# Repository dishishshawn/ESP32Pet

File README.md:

# ESP32PET

An open-source Tamagotchi, built on an ESP32 with an ST7735 LCD and physical buttons. 
A digital pet resembling me responds to feeding, playing, and dressing up. 
Stats are persistent (saved to EEPROM)

## Features
- Deep sleep (Battery powered use)
- Three-button UI (+ 1 for on and off)
- Designed for portable use

## Hardware Requirements
- ESP32 w/ EEPROM storage (ESP32 DevKit V1)
- Arduino framework (Platform IO)
- TFT LCD (ST7735)
- 3.7V LiPo battery + MCP1700 (3.3V LDO)
- 4x momentary push buttons

## Applications
- KiCAD
- Arduino IDE or PlatformIO

## Additional Notes
Decided to use the full esp32 dev kit for easy testing of new firmware/features.

## Images

## Schematic

**Top level**

**ESP32**

**Power**

**TFT LCD**

## Tamagotchi Case
[OnShape](https://cad.onshape.com/documents/7b0af2517bc8518bf7fb4dfa/w/fc1d8dcb5d67add2eca69795/e/ab74bcbcb7495b5b308ae66d)

## Demo

No demo currently

## Sponsorship

PCBWay sponsors 3D Printing and PCB assembly costs on this project during the prototyping phase!
If you are interested in their awesome fabrication services please check them out.  They offer
3D prototyping, PCB design, and assembly, as well as CNC metal fabrication.  Costs are reasonable and the quality is as good as it gets.  Thank you, PCBWay, for sponsoring me!

## License

MIT

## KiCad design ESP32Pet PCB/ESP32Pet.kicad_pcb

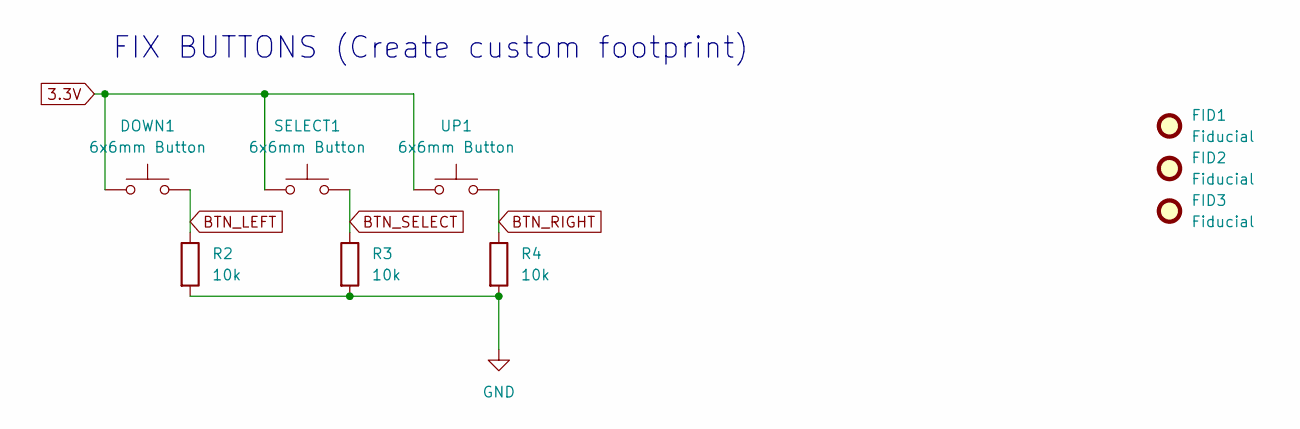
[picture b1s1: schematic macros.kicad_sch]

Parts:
DOWN1: 6x6mm Button; SW_PUSH_6mm_H5mm
FID1, FID2, FID3: Fiducial; Fiducial_0.5mm_Mask1mm
R2, R3, R4: 10k; R_Axial_DIN0204_L3.6mm_D1.6mm_P7.62mm_Horizontal
SELECT1: 6x6mm Button; SW_PUSH_6mm_H5mm
UP1: 6x6mm Button; SW_PUSH_6mm_H5mm

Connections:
3.3V: DOWN1.1, SELECT1.1, UP1.1; also elsewhere on the board
BTN_LEFT: DOWN1.2, R2.1; also elsewhere on the board
BTN_RIGHT: R4.1, UP1.2; also elsewhere on the board
BTN_SELECT: R3.1, SELECT1.2; also elsewhere on the board
GND: R2.2, R3.2, R4.2; also elsewhere on the board

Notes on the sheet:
FIX BUTTONS (Create custom footprint)

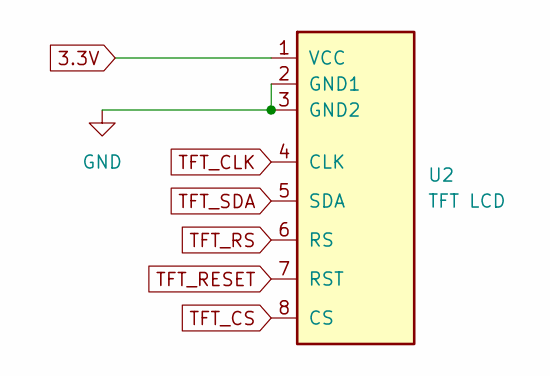
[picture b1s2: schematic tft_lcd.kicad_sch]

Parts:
U2: TFT LCD; TFT LCD 1.8inch 128x160 w_ SD Card Slot

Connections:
3.3V: U2.1 (VCC); also elsewhere on the board
GND: U2.2 (GND1), U2.3 (GND2); also elsewhere on the board
TFT_CLK: U2.4 (CLK); also elsewhere on the board
TFT_CS: U2.8 (CS); also elsewhere on the board
TFT_RESET: U2.7 (RST); also elsewhere on the board
TFT_RS: U2.6 (RS); also elsewhere on the board
TFT_SDA: U2.5 (SDA); also elsewhere on the board

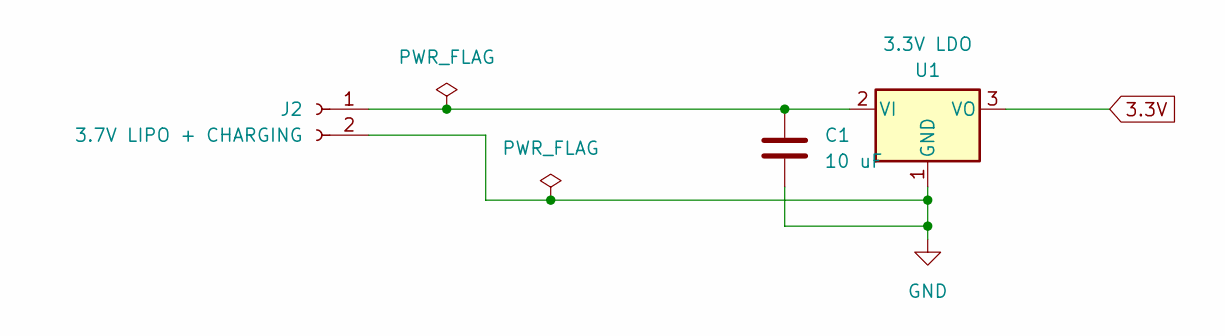
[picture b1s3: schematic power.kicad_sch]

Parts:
C1: 10 uF; CP_Radial_D4.0mm_P1.50mm
J2: 3.7V LIPO + CHARGING; PinHeader_1x02_P2.54mm_Vertical
U1: 3.3V LDO; TO-92_Inline

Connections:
3.3V: U1.3 (VO); also elsewhere on the board
GND: C1.1, J2.2, U1.1 (GND); also elsewhere on the board
unnamed: C1.2, J2.1, U1.2 (VI)

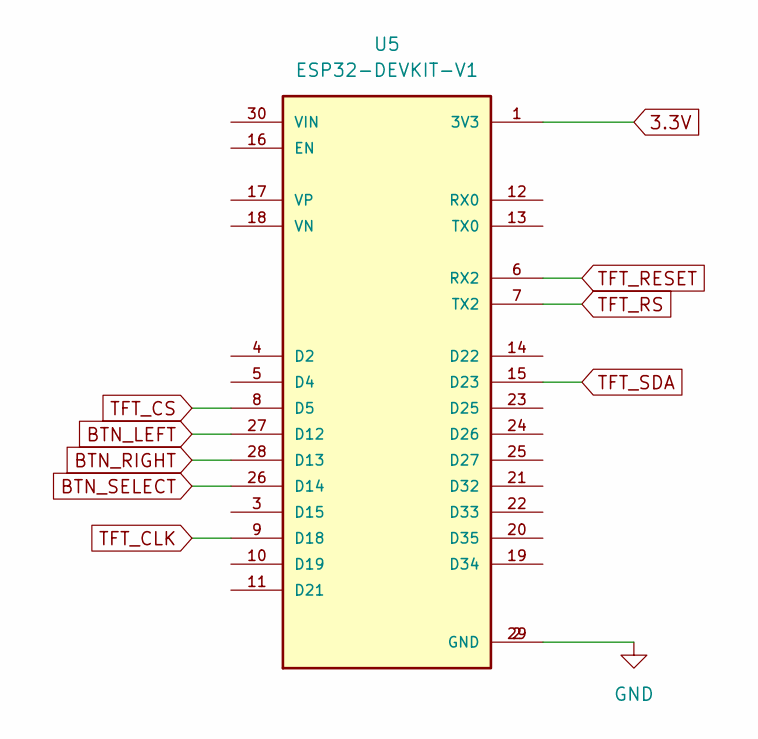
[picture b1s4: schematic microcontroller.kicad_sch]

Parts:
U5: ESP32-DEVKIT-V1; MODULE_ESP32_DEVKIT_V1; PARTREV N/A

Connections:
3.3V: U5.1 (3V3); also elsewhere on the board
BTN_LEFT: U5.27 (D12); also elsewhere on the board
BTN_RIGHT: U5.28 (D13); also elsewhere on the board
BTN_SELECT: U5.26 (D14); also elsewhere on the board
GND: U5.2 (GND), U5.29 (GND); also elsewhere on the board
TFT_CLK: U5.9 (D18); also elsewhere on the board
TFT_CS: U5.8 (D5); also elsewhere on the board
TFT_RESET: U5.6 (RX2); also elsewhere on the board
TFT_RS: U5.7 (TX2); also elsewhere on the board
TFT_SDA: U5.15 (D23); also elsewhere on the board

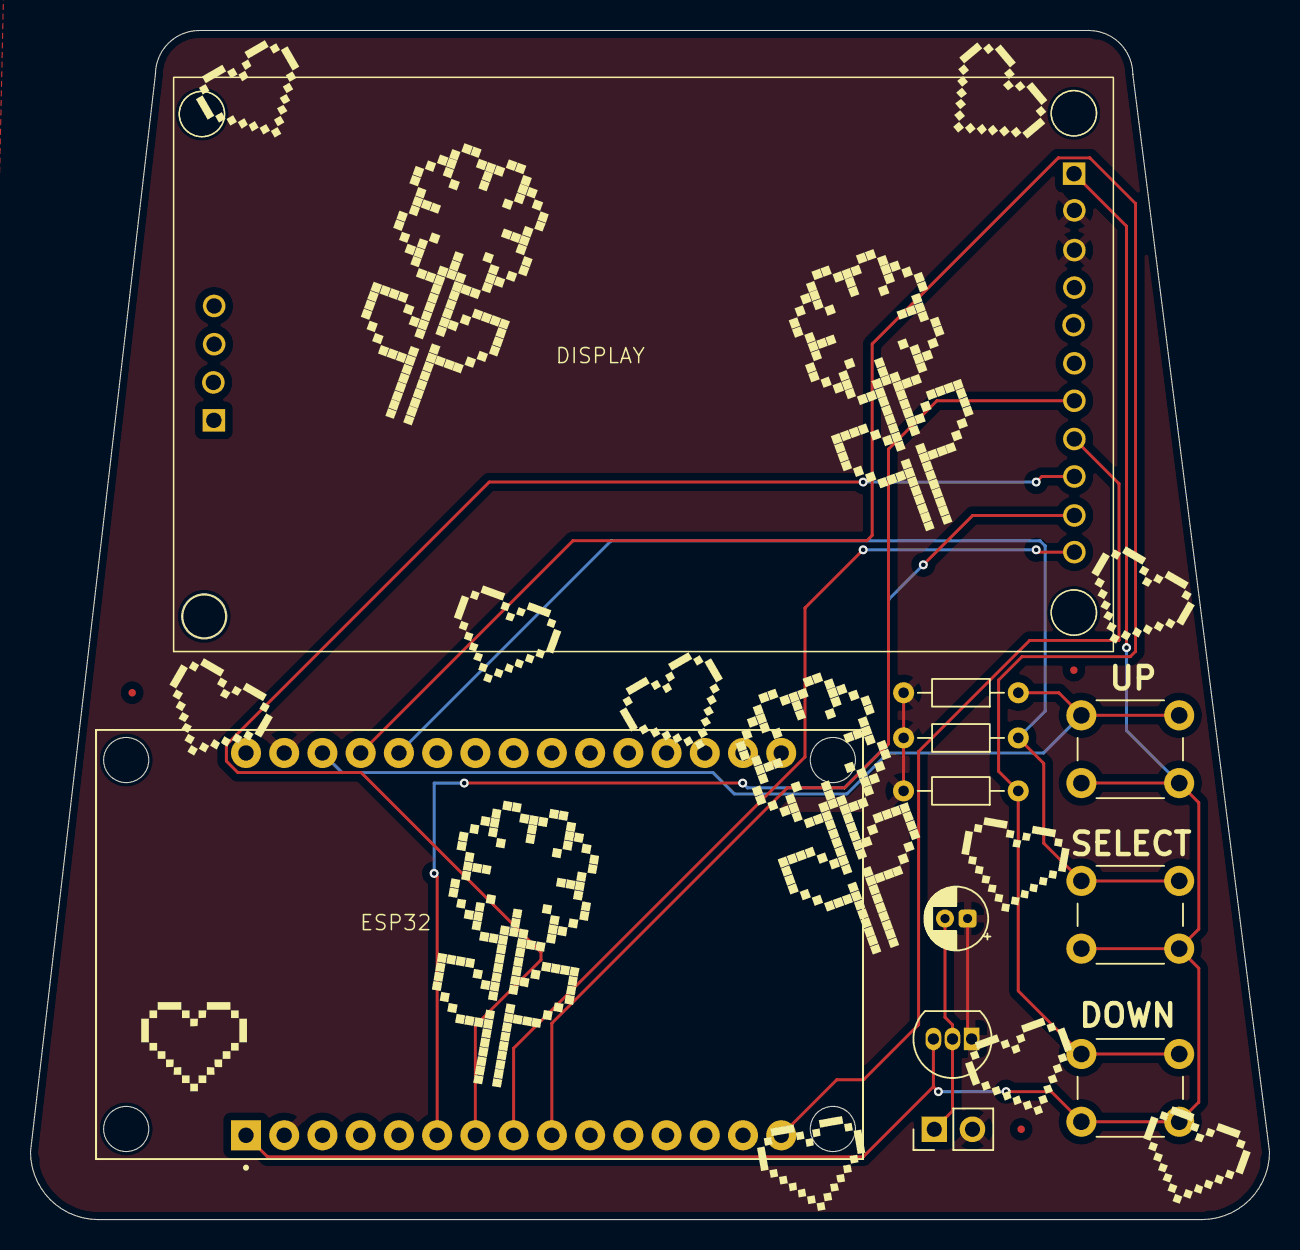
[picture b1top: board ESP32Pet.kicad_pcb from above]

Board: 2 copper layers, 82.3 x 79.0 mm, 14 parts (0 on the bottom side), 11 nets.

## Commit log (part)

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2025-05-28 Added Gotchi library
2025-05-28 Added scroll menu library
2025-05-28 Display works, needs to be scaled to fit screen, and there are visual bugs
2025-05-29 Working eat, play, cut screens, but dress screen isn't working. Also, sleep isn't functional
2025-05-29 Fixed and centered the menu
2025-05-29 Menu and menu functions working as intended. Added 200ms delay between scene changes. Next: write data to memory before turning off
2025-05-29 Semi-working memory, it reads correctly on startup, but values are reset right after
2025-05-29 Fully working memory, only changes needed are for sleep mode
2025-05-29 Working version
2025-06-01 Added KiCAD files
2025-06-03 Schematic Updated
2025-06-03 Schematic complete, created custom footprints and symbols for TFT LCD
2025-06-03 PCB Design Complete
2025-06-12 Updated ST7735S Footprint for bigger through holes
2025-06-12 Updated ST7735 footprint
